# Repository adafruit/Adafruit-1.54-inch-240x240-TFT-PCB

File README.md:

## Adafruit 1.54" 240x240 Wide Angle TFT LCD Display with MicroSD - ST7789 PCB

<a href="http://www.adafruit.com/products/3787"><br/>
Click here to purchase one from the Adafruit shop</a>

PCB files for the Adafruit 1.54" 240x240 Wide Angle TFT LCD Display with MicroSD - ST7789. Format is EagleCAD schematic and board layout
* https://www.adafruit.com/product/3787

### Description

We've been looking for a display like this for a long time - it's only 1.5" diagonal but has a high density 220 ppi, 240x240 pixel display with full-angle viewing. It looks a lot like our 1.44" 128x128 display, but has 4x as many pixels and looks great at any angle. We've seen displays of this caliber used in smartwatches and small electronic devices but they've always been MIPI interface. Finally, we found one that is SPI and has a friendly display driver, so it works with any and all microcontrollers or microcomputers!

This lovely little display breakout is the best way to add a small, colorful and very bright display to any project. Since the display uses 4-wire SPI to communicate and has its own pixel-addressable frame buffer, it can be used with every kind of microcontroller. Even a very small one with low memory and few pins available! The 1.54" display has 240x240 16-bit full color pixels and is an **IPS** display, so the color looks great up to 80 degrees off axis in any direction. The TFT driver (ST7789) is very similar to the popular ST7735, and our Arduino library supports it well.

Our breakout has the TFT display soldered on (it uses a delicate flex-circuit connector) as well as a ultra-low-dropout 3.3V regulator and a 3/5V level shifter so you can use it with 3.3V or 5V power and logic. We also had a little space so we placed a microSD card holder so you can easily load full color bitmaps from a FAT16/FAT32 formatted microSD card. The microSD card is not included, [but you can pick one up here](http://www.adafruit.com/products/102) .

Of course, we wouldn't just leave you with a datasheet and a "good luck!" - [we've written a full open source graphics library that can draw pixels, lines, rectangles, circles, text and bitmaps as well as example code and a wiring tutorial.](http://learn.adafruit.com/1-8-tft-display) The code is written for Arduino but can be easily ported to your favorite microcontroller!

**Please note!** This display is designed original for smart watches and similar, where there's a glass over the screen. Without something gently holding the screen down, the backlight can eventually peel away from the TFT. (It's not destructive but it's unattractive) You can prevent this by, ideally, adding a plastic or glass cover/overlay. If using bare, try dabbing a touch of T6000 or similar craft glue on the thin side edges, or using a thin piece of tape to keep the front TFT attached to the backlight. We're trying to find a display without this annoyance, but these displays don't have a lot of manufacturers so pickin's are slim!

### License

Adafruit invests time and resources providing this open source design, please support Adafruit and open-source hardware by purchasing products from [Adafruit](https://www.adafruit.com)!

Designed by Limor Fried/Ladyada for Adafruit Industries.

Creative Commons Attribution/Share-Alike, all text above must be included in any redistribution. See license.txt for additional details.

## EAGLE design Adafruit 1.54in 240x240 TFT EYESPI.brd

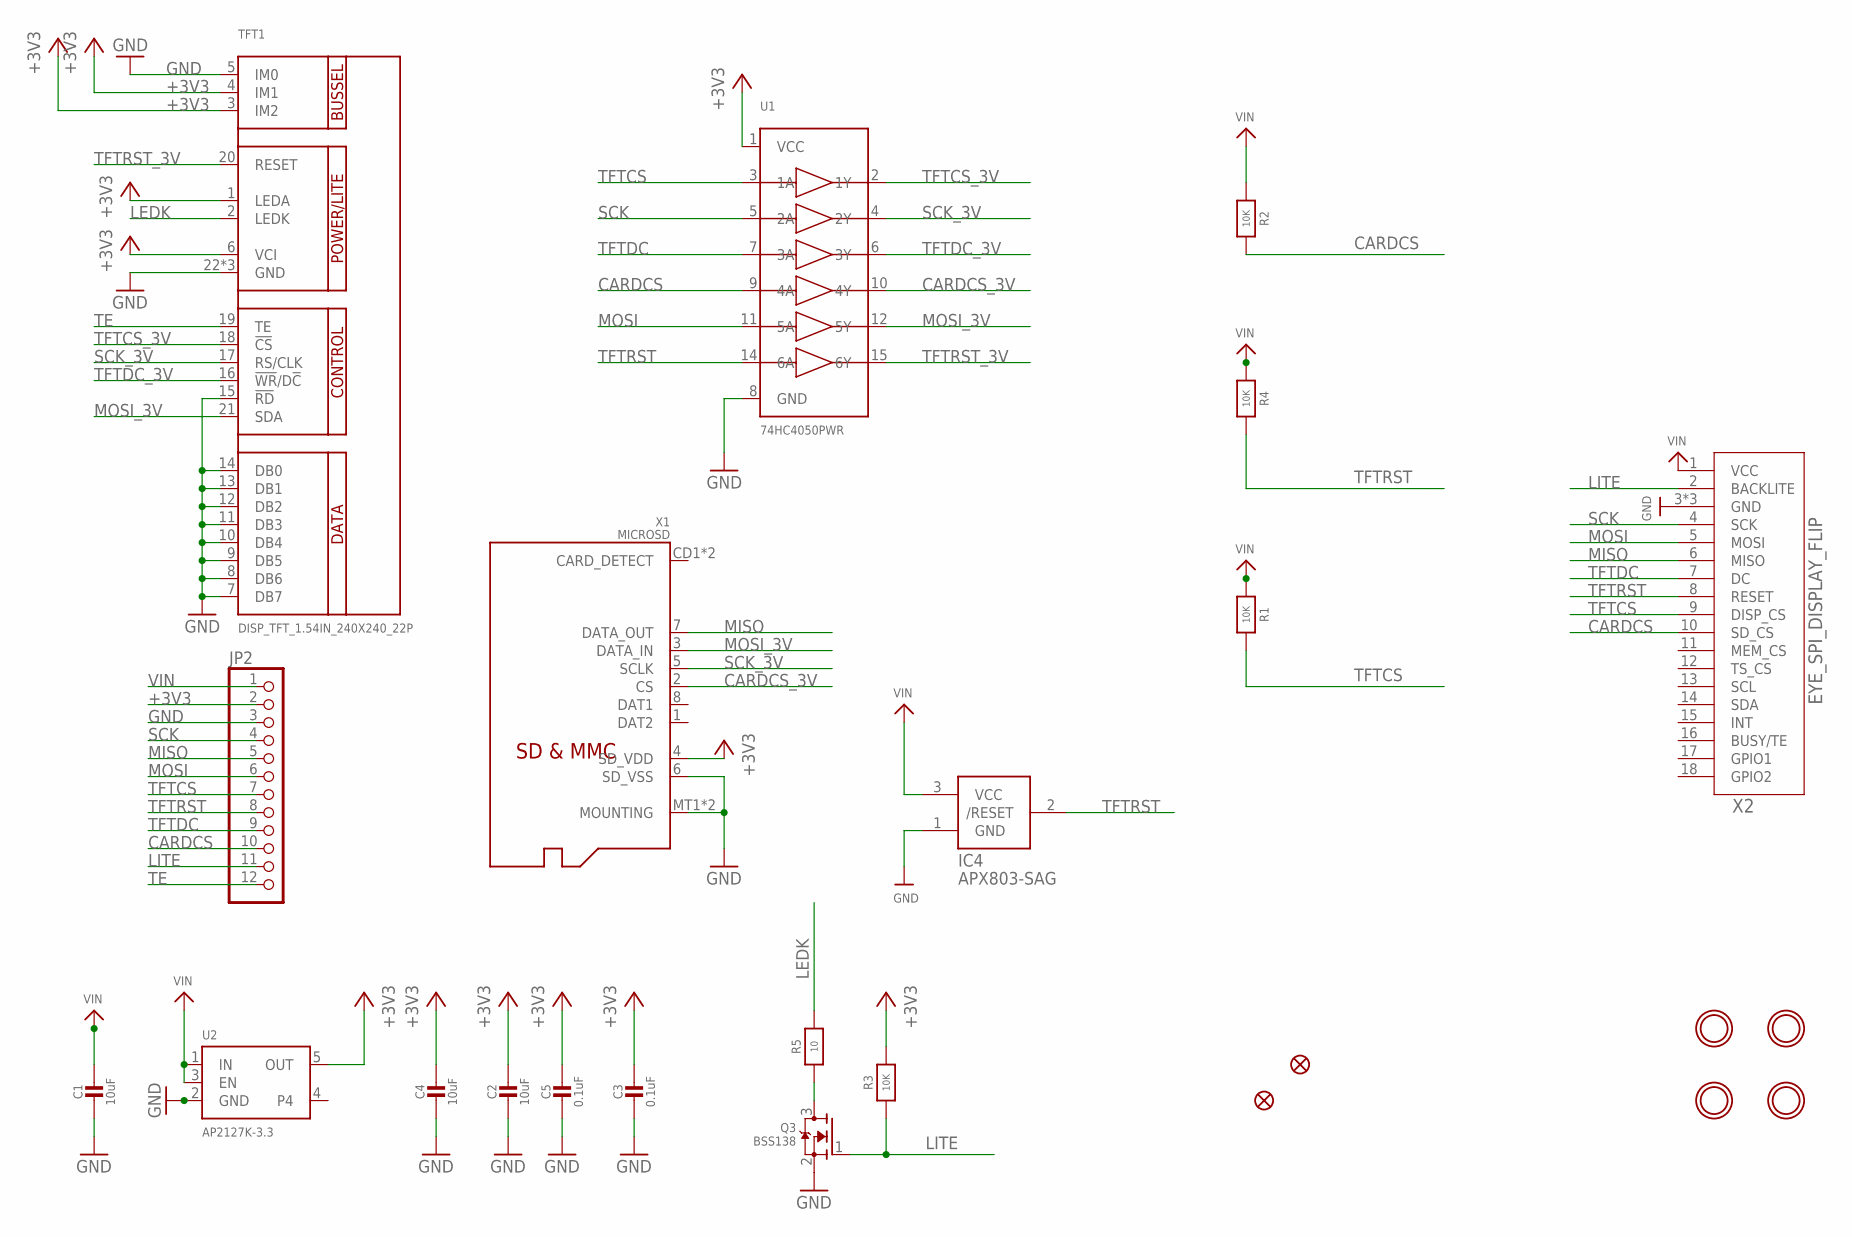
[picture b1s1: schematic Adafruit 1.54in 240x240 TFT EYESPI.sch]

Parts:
C1, C2, C4: 10uF; 0805-NO
C3, C5: 0.1uF; 0603-NO
IC4: APX803-SAG; SOT23-WIDE
JP2: HEADER-1X1276MIL; 1X12_ROUND_76MIL
Q3: BSS138; SOT23-WIDE
R1, R2, R3, R4: 10K; 0603-NO
R5: 10; 0603-NO
TFT1: DISP_TFT_1.54IN_240X240_22P; TFT_1.54IN_240X240_22PIN
U1: 74HC4050PWR; TSSOP16
U2: AP2127K-3.3; SOT23-5
U$4, U$5: FIDUCIAL_1MM
U$7, U$8, U$9, U$10: MOUNTINGHOLE2.5; MOUNTINGHOLE_2.5_PLATED
X1: MICROSD
X2: EYE_SPI_DISPLAY_FLIP; EYE_SPI_DISPLAY_BOTCONTACT

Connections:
+3V3: C2.1, C3.1, C4.1, C5.1, JP2.2, R3.2, TFT1.1 (LEDA), TFT1.3 (IM2), TFT1.4 (IM1), TFT1.6 (VCI), U1.1 (VCC), U2.5 (OUT), X1.4 (SD_VDD)
CARDCS: JP2.10, R2.1, U1.9 (4A), X2.10 (SD_CS)
CARDCS_3V: U1.10 (4Y), X1.2 (CS)
GND: C1.2, C2.2, C3.2, C4.2, C5.2, IC4.1 (GND), JP2.3, Q3.2 (S), TFT1.5 (IM0), TFT1.7 (DB7), TFT1.8 (DB6), TFT1.9 (DB5), TFT1.10 (DB4), TFT1.11 (DB3), TFT1.12 (DB2), TFT1.13 (DB1), TFT1.14 (DB0), TFT1.15 (!RD), TFT1.22 (GND), TFT1.SUPPORT1 (GND), TFT1.SUPPORT2 (GND), U1.8 (GND), U2.2 (GND), X1.6 (SD_VSS), X1.MT1 (MOUNTING), X1.MT2 (MOUNTING), X2.3 (GND), X2.SUPPORT1 (GND), X2.SUPPORT2 (GND)
LEDK: R5.2, TFT1.2 (LEDK)
LITE: JP2.11, Q3.1 (G), R3.1, X2.2 (BACKLITE)
MISO: JP2.5, X1.7 (DATA_OUT), X2.6 (MISO)
MOSI: JP2.6, U1.11 (5A), X2.5 (MOSI)
MOSI_3V: TFT1.21 (SDA), U1.12 (5Y), X1.3 (DATA_IN)
unnamed: Q3.3 (D), R5.1
SCK: JP2.4, U1.5 (2A), X2.4 (SCK)
SCK_3V: TFT1.17 (RS/CLK), U1.4 (2Y), X1.5 (SCLK)
TE: JP2.12, TFT1.19 (TE)
TFTCS: JP2.7, R1.1, U1.3 (1A), X2.9 (DISP_CS)
TFTCS_3V: TFT1.18 (!CS), U1.2 (1Y)
TFTDC: JP2.9, U1.7 (3A), X2.7 (DC)
TFTDC_3V: TFT1.16 (!WR!/D!C), U1.6 (3Y)
TFTRST: IC4.2 (/RESET), JP2.8, R4.1, U1.14 (6A), X2.8 (RESET)
TFTRST_3V: TFT1.20 (RESET), U1.15 (6Y)
VIN: C1.1, IC4.3 (VCC), JP2.1, R1.2, R2.2, R4.2, U2.1 (IN), U2.3 (EN), X2.1 (VCC)

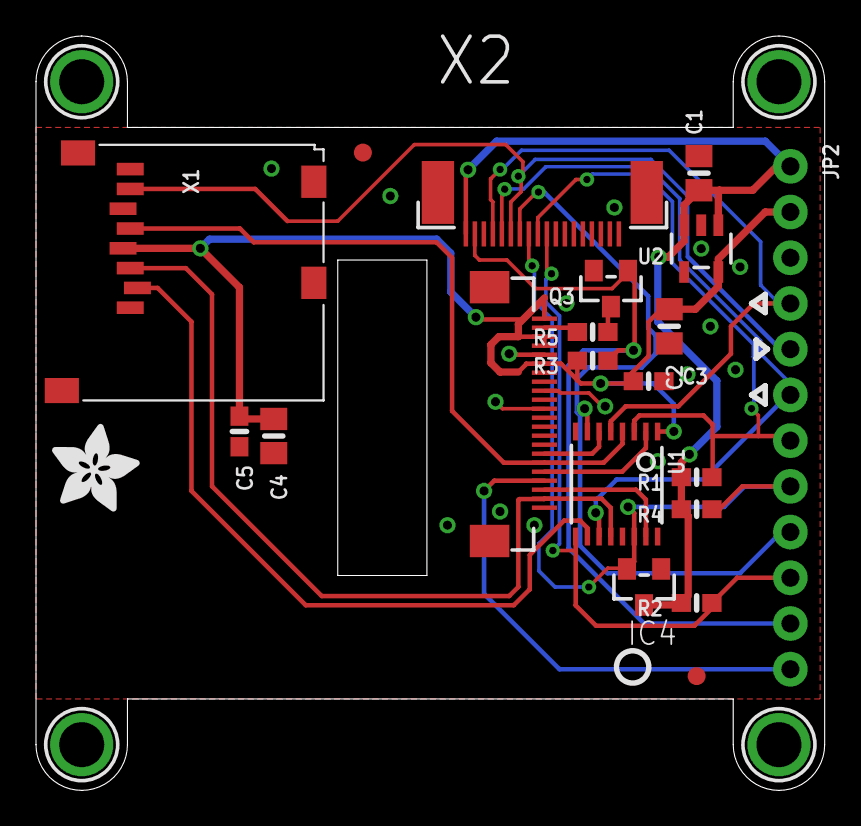
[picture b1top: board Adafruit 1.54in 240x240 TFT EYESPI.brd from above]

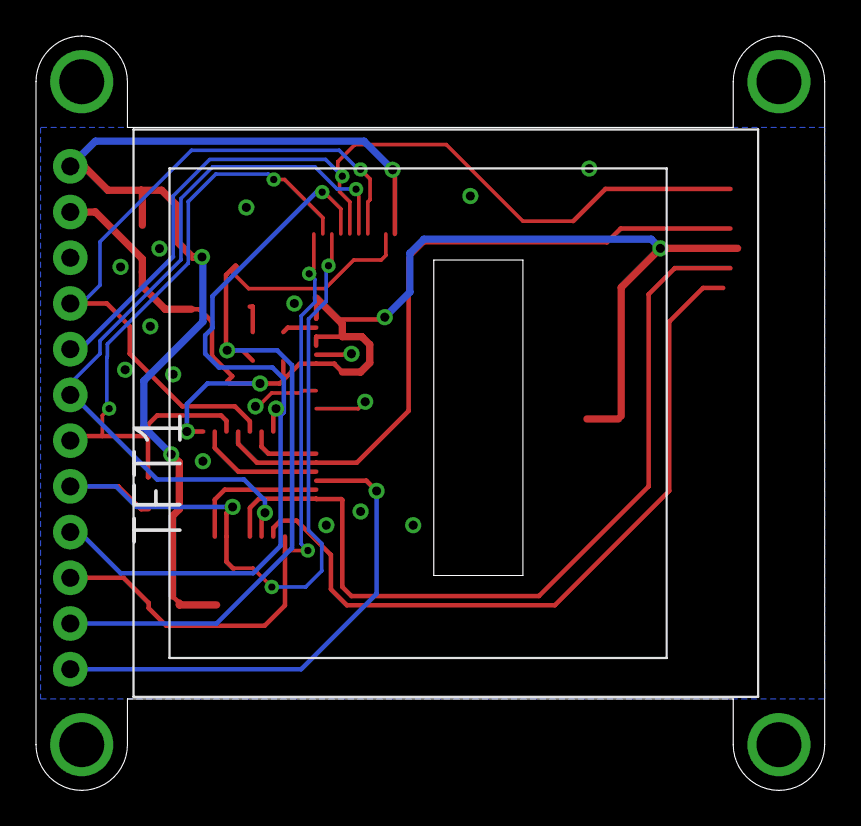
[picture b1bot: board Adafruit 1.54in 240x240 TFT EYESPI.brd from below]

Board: 2 copper layers, 43.8 x 41.9 mm, 56 parts (14 on the bottom side), 20 nets.

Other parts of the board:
PLABEL0: PLABEL0
PLABEL1: PLABEL1
PLABEL2: PLABEL2
PLABEL3: PLABEL3
PLABEL4: PLABEL4
PLABEL5: PLABEL5
PLABEL6: PLABEL6
PLABEL7: PLABEL7
PLABEL8: PLABEL8
PLABEL9: PLABEL9
PLABEL10: PLABEL10
PLABEL11: PLABEL11
PLABEL12: PLABEL12
PLABEL13: PLABEL13
PLABEL14: PLABEL14
PLABEL15: PLABEL15
PLABEL16: PLABEL16
PLABEL17: PLABEL17
PLABEL18: PLABEL18
PLABEL19: PLABEL19
PLABEL20: PLABEL20
PLABEL21: PLABEL21
PLABEL22: PLABEL22
PLABEL23: PLABEL23
PLABEL24: PLABEL24
PLABEL25: PLABEL25
PLABEL26: PLABEL26
PLABEL27: PLABEL27
PLABEL28: PLABEL28
PLABEL29: PLABEL29
U$1: ADAFRUIT_5MM
U$2: PCBFEAT-REV-040

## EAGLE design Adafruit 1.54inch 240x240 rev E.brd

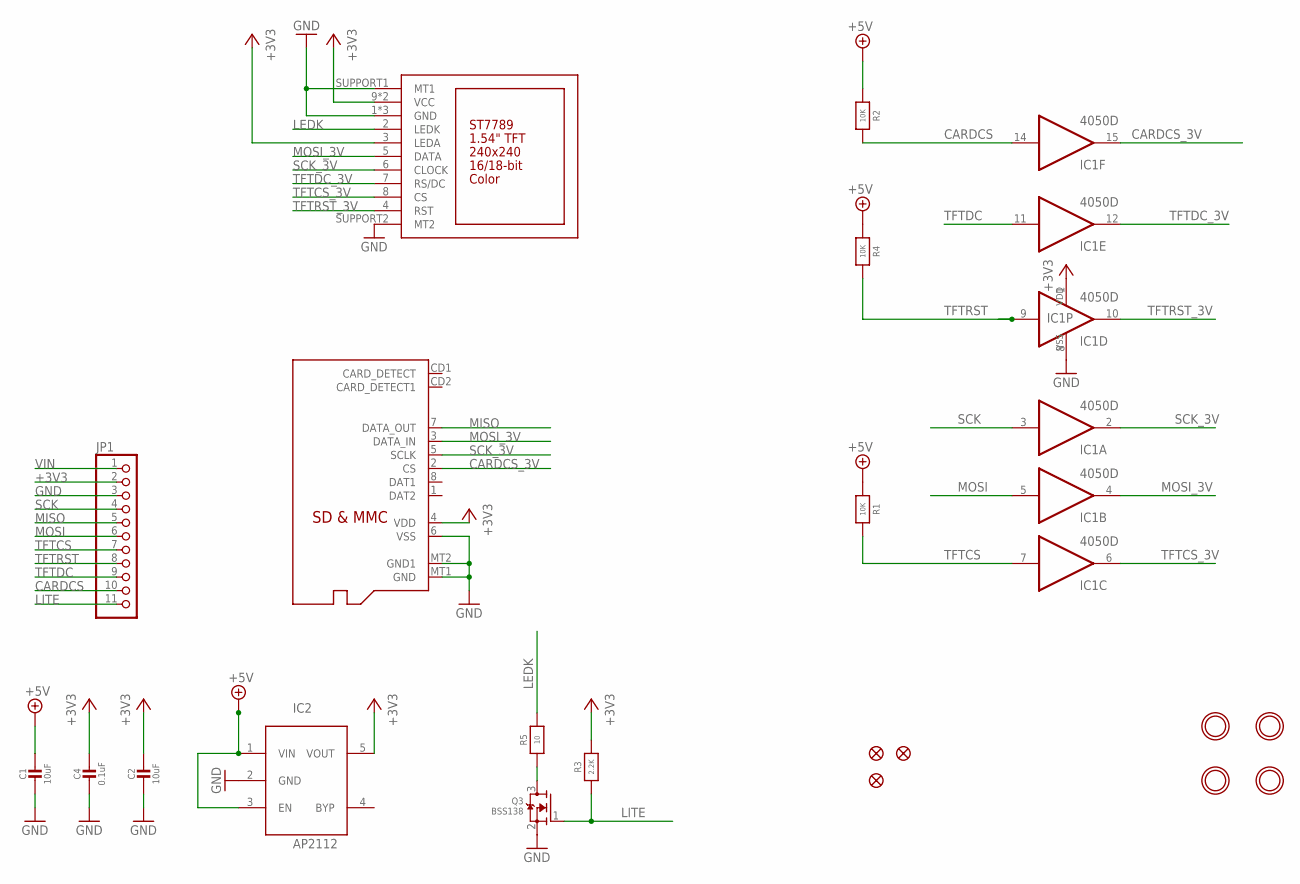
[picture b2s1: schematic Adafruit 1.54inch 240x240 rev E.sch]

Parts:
C1, C2: 10uF; 0805-NO
C4: 0.1uF; 0805-NO
DISP1: DISP_LCD_ST7789_1.54IN; TFT_1.54IN_240X240
IC1: 4050D; SO16
IC2: AP2112; SOT23-5L
JP1: HEADER-1X1176MIL; 1X11_ROUND_76
Q2: MICROSD
Q3: BSS138; SOT23-WIDE
R1, R2, R4: 10K; 0805-NO
R3: 2.2K; 0805-NO
R5: 10; 0805-NO
U$3, U$4, U$5: FIDUCIAL_1MM
U$7, U$8, U$9, U$10: MOUNTINGHOLE2.5; MOUNTINGHOLE_2.5_PLATED

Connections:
+3V3: C2.1, C4.1, DISP1.3 (LEDA), DISP1.9 (VCC), DISP1.10 (VCC), IC1.1 (VDD), IC2.5 (VOUT), JP1.2, Q2.4 (VDD), R3.2
CARDCS: IC1.14 (I), JP1.10, R2.1
CARDCS_3V: IC1.15 (O), Q2.2 (CS)
GND: C1.2, C2.2, C4.2, DISP1.1 (GND), DISP1.11 (GND), DISP1.12 (GND), DISP1.SUPPORT1 (MT1), DISP1.SUPPORT2 (MT2), IC1.8 (VSS), IC2.2 (GND), JP1.3, Q2.6 (VSS), Q2.MT1 (GND), Q2.MT2 (GND1), Q3.2 (S)
LEDK: DISP1.2 (LEDK), R5.2
LITE: JP1.11, Q3.1 (G), R3.1
MISO: JP1.5, Q2.7 (DATA_OUT)
MOSI: IC1.5 (I), JP1.6
MOSI_3V: DISP1.5 (DATA), IC1.4 (O), Q2.3 (DATA_IN)
unnamed: Q3.3 (D), R5.1
SCK: IC1.3 (I), JP1.4
SCK_3V: DISP1.6 (CLOCK), IC1.2 (O), Q2.5 (SCLK)
TFTCS: IC1.7 (I), JP1.7, R1.1
TFTCS_3V: DISP1.8 (CS), IC1.6 (O)
TFTDC: IC1.11 (I), JP1.9
TFTDC_3V: DISP1.7 (RS/DC), IC1.12 (O)
TFTRST: IC1.9 (I), JP1.8, R4.1
TFTRST_3V: DISP1.4 (RST), IC1.10 (O)
VIN: C1.1, IC2.1 (VIN), IC2.3 (EN), JP1.1, R1.2, R2.2, R4.2

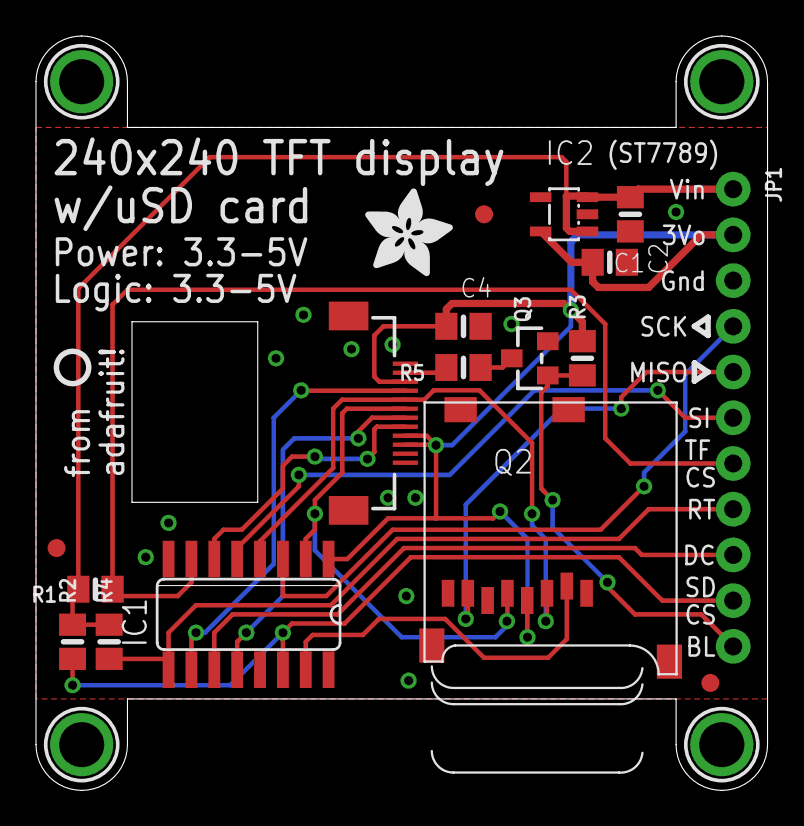
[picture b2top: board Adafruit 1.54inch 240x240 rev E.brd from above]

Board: 2 copper layers, 40.6 x 41.9 mm, 23 parts (1 on the bottom side), 19 nets.

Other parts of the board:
U$1: ADAFRUIT_5MM
U$2: PCBFEAT-REV-040

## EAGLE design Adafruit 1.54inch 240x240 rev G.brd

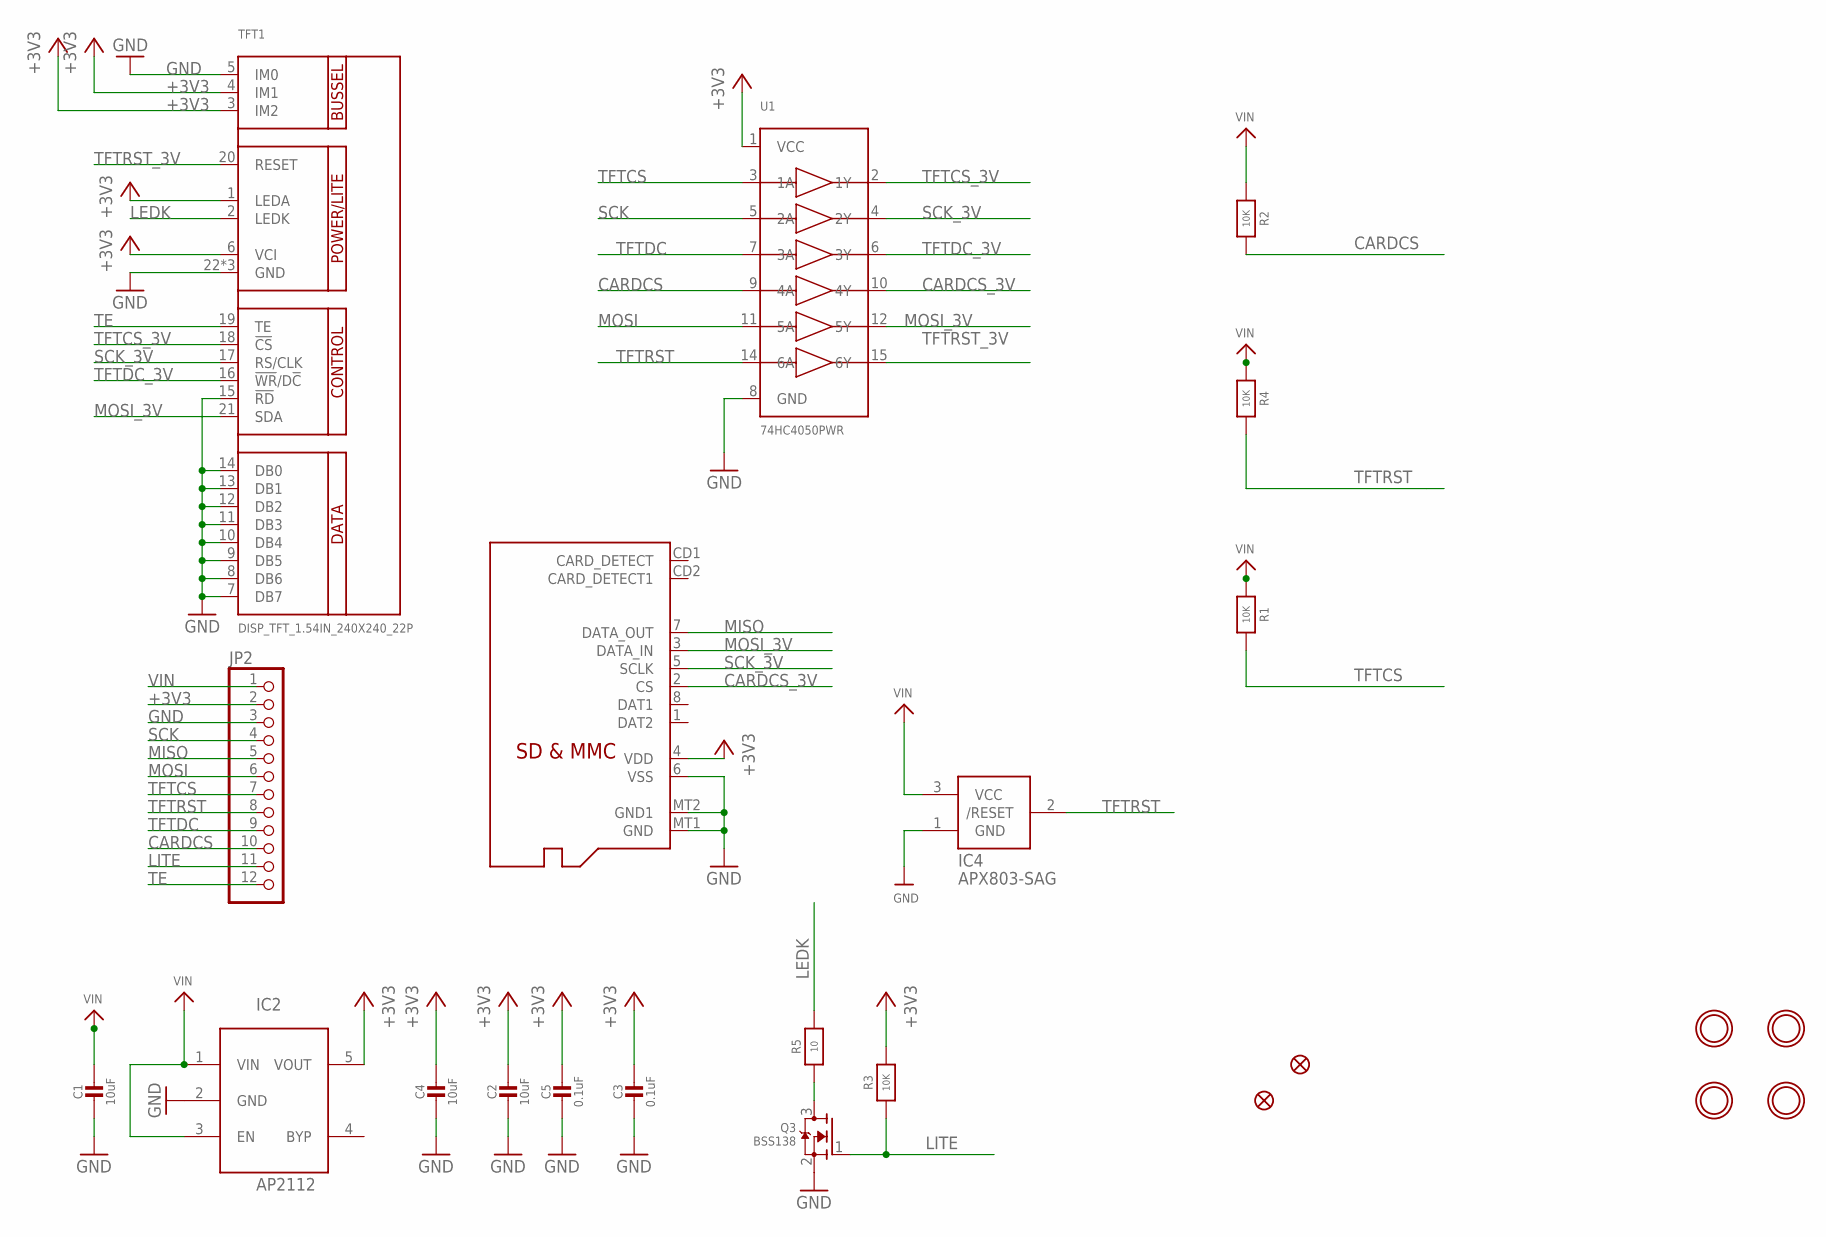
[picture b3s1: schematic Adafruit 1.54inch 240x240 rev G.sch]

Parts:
C1, C2, C4: 10uF; 0805-NO
C3, C5: 0.1uF; 0603-NO
IC2: AP2112; SOT23-5L
IC4: APX803-SAG; SOT23
JP2: HEADER-1X1276MIL; 1X12_ROUND_76MIL
Q2: MICROSD
Q3: BSS138; SOT23-WIDE
R1, R2, R3, R4: 10K; 0603-NO
R5: 10; 0603-NO
TFT1: DISP_TFT_1.54IN_240X240_22P; TFT_1.54IN_240X240_22PIN
U1: 74HC4050PWR; TSSOP16
U$4, U$5: FIDUCIAL_1MM
U$7, U$8, U$9, U$10: MOUNTINGHOLE2.5; MOUNTINGHOLE_2.5_PLATED

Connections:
+3V3: C2.1, C3.1, C4.1, C5.1, IC2.5 (VOUT), JP2.2, Q2.4 (VDD), R3.2, TFT1.1 (LEDA), TFT1.3 (IM2), TFT1.4 (IM1), TFT1.6 (VCI), U1.1 (VCC)
CARDCS: JP2.10, R2.1, U1.9 (4A)
CARDCS_3V: Q2.2 (CS), U1.10 (4Y)
GND: C1.2, C2.2, C3.2, C4.2, C5.2, IC2.2 (GND), IC4.1 (GND), JP2.3, Q2.6 (VSS), Q2.MT1 (GND), Q2.MT2 (GND1), Q3.2 (S), TFT1.5 (IM0), TFT1.7 (DB7), TFT1.8 (DB6), TFT1.9 (DB5), TFT1.10 (DB4), TFT1.11 (DB3), TFT1.12 (DB2), TFT1.13 (DB1), TFT1.14 (DB0), TFT1.15 (!RD), TFT1.22 (GND), TFT1.SUPPORT1 (GND), TFT1.SUPPORT2 (GND), U1.8 (GND)
LEDK: R5.2, TFT1.2 (LEDK)
LITE: JP2.11, Q3.1 (G), R3.1
MISO: JP2.5, Q2.7 (DATA_OUT)
MOSI: JP2.6, U1.11 (5A)
MOSI_3V: Q2.3 (DATA_IN), TFT1.21 (SDA), U1.12 (5Y)
unnamed: Q3.3 (D), R5.1
SCK: JP2.4, U1.5 (2A)
SCK_3V: Q2.5 (SCLK), TFT1.17 (RS/CLK), U1.4 (2Y)
TE: JP2.12, TFT1.19 (TE)
TFTCS: JP2.7, R1.1, U1.3 (1A)
TFTCS_3V: TFT1.18 (!CS), U1.2 (1Y)
TFTDC: JP2.9, U1.7 (3A)
TFTDC_3V: TFT1.16 (!WR!/D!C), U1.6 (3Y)
TFTRST: IC4.2 (/RESET), JP2.8, R4.1, U1.14 (6A)
TFTRST_3V: TFT1.20 (RESET), U1.15 (6Y)
VIN: C1.1, IC2.1 (VIN), IC2.3 (EN), IC4.3 (VCC), JP2.1, R1.2, R2.2, R4.2

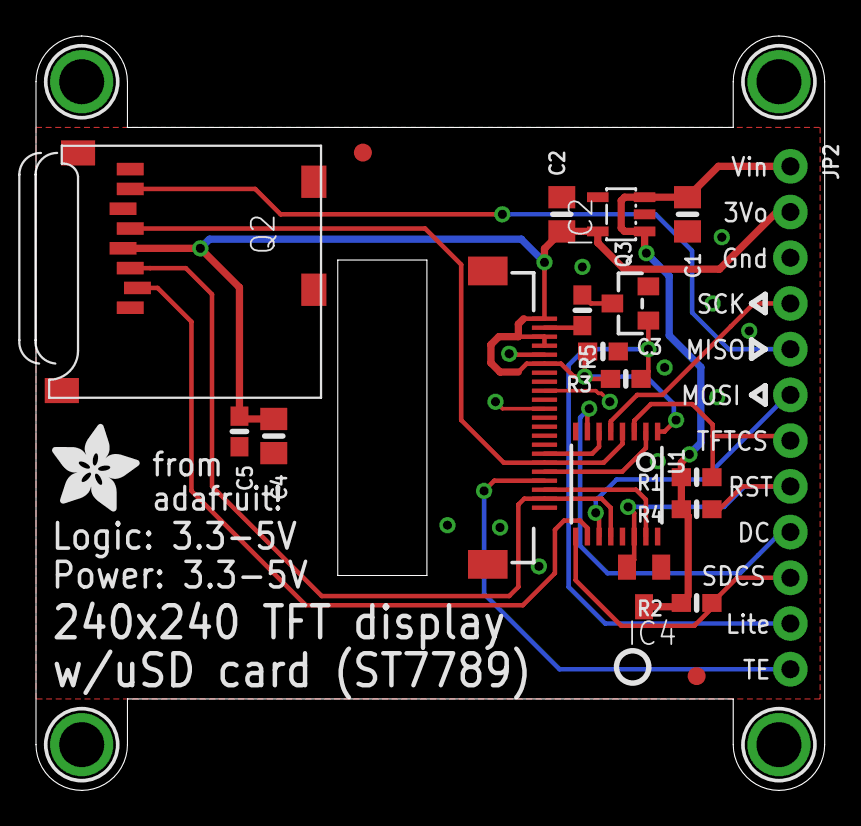
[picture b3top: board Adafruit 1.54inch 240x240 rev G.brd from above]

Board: 2 copper layers, 43.8 x 41.9 mm, 25 parts (1 on the bottom side), 20 nets.

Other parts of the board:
U$1: ADAFRUIT_5MM
U$2: PCBFEAT-REV-040

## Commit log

2018-09-12 init
2019-07-16 updated to use new pcb repo cookiecutter
2019-08-07 Updating board files.
2019-08-08 Removing to update to current version
2019-08-08 Adding updated photo
2019-09-09 add rev G with 22pin display
2020-06-29 Add rev E board files.
2023-07-24 Add updated board files.

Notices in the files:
parts and their libraries:
microbuilder: This work is placed in the public domain, and may be freely used for commercial and non-commercial work with the following conditions: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
